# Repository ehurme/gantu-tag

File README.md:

<h1 align="center">gantu-tag · ಗಂಟು</h1>

<p align="center"><b>Open, tiny Bluetooth LE tracking tags for insects that anyone can order from JLCPCB.</b></p>

*Gantu* (ಗಂಟು, said *gun-two*) is Kannada for a knot, for someone who clings on and goes wherever you go, and for
a node.
[More about the name](#about-the-name).

**Website:** https://pvnkmrksk.github.io/gantu-tag/ · **Build guide:** [step by step](docs/guide.md)
([on the website](https://pvnkmrksk.github.io/gantu-tag/guide.html), with a form that turns your key into a config) ·
**Dashboard:** [Gantumoote](https://github.com/pvnkmrksk/gantumoote), self-hosted on a Pi or laptop

These are **early pilots**. The first panels were ordered on 6 November 2026 and arrived assembled on 19 November;
bench testing has started. **First result, the same evening:** a Hagalu S6, configured over UART and run from RAM
with a plain copper antenna, was picked up by passing iPhones and reported through Apple Find My three times in
20 minutes (±76–102 m). It advertised steadily from about 1.9 klx, and weighs **0.242 g** with its wire antenna
(tail cut, no epoxy). Treat every other number here as a design estimate until bring-up is complete.

**First walk, 20 November:** two burned Hagalu tags, running on light alone, went for a walk through town: one on
Apple Find My, one on Hubble. Both were reported, including from inside a supermarket under ordinary shop lighting.
Find My gave well over a hundred sightings in the afternoon; Hubble gave fewer (25 packets), but each one carried the
relaying phone's GPS fix and the tag's own encrypted payload: supply voltage and temperature.

| Find My: the track | Find My: sightings | Hubble: a packet and its decoded payload |
|---|---|---|
|  |  |  |

| Weighed: 0.242 g | Advertising Find My under 1.7 klx |
|---|---|
|  |  |

## The two tags

| | **Hagalu Gantu** · ಹಗಲು ಗಂಟು | **Irulu Gantu** · ಇರುಳು ಗಂಟು |
|---|---|---|
| Power | Six photodiodes charge a 100 µF capacitor; no battery | A silver-oxide button cell (337, 364 or 377) |
| When it runs | **In light only**, in bursts as the capacitor fills | Continuously until the cell is flat (≈ 57 days on a 337 at a 3 s interval) |
| Size (after cutting the tail) | 6.4 × 12.55 mm | Ø 7.2 mm |
| Mass (0.6 mm board) | **0.242 g measured** (S6 with wire, no epoxy; estimate was 0.19–0.21 g) | ≈ 0.12 g without the cell, ≈ 0.25 g with a 337 (estimate) |
| **Cost per tag** (approx.) | **≈ €7** | **≈ €2.30** + a button cell |
| Start-up | On S6/S6L a supervisor starts the radio once the capacitor holds a burst; N6 has none | Fit the cell (V1), or cut the tail (V2) |
| Pilot variants on the panel | S6, S6L, N6 | V1, V2 |
| Design files | [`hagalu/`](hagalu/) | [`irulu/`](irulu/) |

### Renders

KiCad 10 renders of the v8.3 boards as ordered. Top: parts side. Bottom: the antenna pads on Hagalu, and the cell
pads on Irulu.

| | Top | Bottom |
|---|---|---|
| **Hagalu Gantu** |  |  |
| **Irulu Gantu** |  |  |

The JLC panel (94.9 × 71.1 mm, 0.6 mm), with 10 Hagalu and 8 Irulu tags on each panel:

The pilot variant names (S6, S6L, N6, V1, V2) only mark the start-circuit options under test. They'll be narrowed
down once the first tags are on the bench.

## Approach

The tag doesn't carry a GPS or a receiver. It only **broadcasts a Bluetooth LE advert every few seconds**, and phones
or gateways that belong to a large existing network hear it and report where they were. You then fetch those
reports.

- **One chip, configured rather than programmed.** Both tags use the InPlay
  [IN100 NanoBeacon](https://inplay-tech.com/in100). It runs no firmware: you load a configuration over its UART
  (address, advert bytes, interval, TX power), test it in RAM, then burn it once into the chip's one-time-programmable
  memory. That keeps the tag down to the chip, a crystal and a few capacitors.
- **Two networks, the same hardware.** Which network a tag joins is decided only by what you burn into it:
  - **Apple Find My** via [OpenHaystack](https://github.com/seemoo-lab/openhaystack): the tag sends a fixed-key
    Find My advert, nearby iPhones relay its position to Apple, and you decrypt the reports with your private key.
    No Apple hardware is needed on the tag side, and it costs nothing per tag.
  - **[Hubble Network](https://hubble.com)**: the IN100 is one of Hubble's supported chips, and its adverts are picked
    up by Hubble's terrestrial network of phones and gateways and, as its next satellites arrive, from orbit. Hubble
    is a paid service with a free starter tier.
- **Built by JLCPCB, finished by hand.** Every part is placed by JLCPCB's assembly service from its own stock, on a
  2-layer 0.6 mm board. You add only the antenna wire, the cell (Irulu) and epoxy.
- **Started by cutting.** Each tag carries its programming pads on a tail. Like commercial bat and insect tags, you
  program it, then cut the tail off; on Irulu V2 the cut is also what switches it on.
- **Pilots before a batch.** The first panel carries several population variants of each tag (S6/S6L/N6 and V1/V2),
  so one order shows which start circuit works before anyone orders in bulk.

## Build your own

The [build guide](docs/guide.md) walks through every step, with photos. In short:

1. **Order** the files in [`order/`](order/) from JLCPCB: 0.6 mm, Panel by Customer, Standard PCBA, 2 assembled
   panels. One order gives 20 Hagalu and 16 Irulu tags.
2. **Fit the antenna:** a 31 mm, ≈ 0.1 mm wire on the **ANT** pad, and a second one on **GND** for a dipole.
3. **Make the jig:** four jumper wires, a 2 × 2 block of header pins and a rubber band. The pins wedge into the
   tail's four 0.8 mm holes and hold by themselves.
4. **Make the config:** take a template from [`configs/`](configs/) and add your key, from Find My (you generate it)
   or Hubble (it issues one). Use `tools/new_findmy_tag.py` or `tools/new_hubble_tag.py`, or the website's form.
5. **Program:** InPlay's NanoBeacon Config Tool. Test in RAM, then burn the one-time-programmable memory
   ([details](docs/programming.md)).
6. **Finish:** fit the cell on Irulu, cut the tail, coat in epoxy. Then follow the tag through Find My or Hubble.

| The jig | Wiring: tail → 3.3 V USB-serial adapter |
|---|---|
|  | **G** (square hole) → GND<br>**+** → 3V3 (never 5 V)<br>**R** → TXD<br>**T** → RXD<br><br>Seat the jig first, then plug in the USB. |

## Follow your tags

[Gantumoote](https://github.com/pvnkmrksk/gantumoote), the self-hosted dashboard in its own repository, is the map we used for the first walk. Run it on a laptop or leave
it collecting on a Raspberry Pi. It handles Find My and Hubble in the same device list, including voltage,
temperature and advert count from the Gantu Hubble payload. Each tag keeps its own history. Your keys, history
and logs stay on the host. A Pi can start collecting at boot and keep the same HTTPS address through a named tunnel.

## Roadmap

Lighter first, then simpler, then cheaper. The full plan, with mass targets, is in [`docs/roadmap.md`](docs/roadmap.md).

| Stage | What | Hagalu | Irulu (with a 337) |
|---|---|---|---|
| **Now** | Bench work on the v8.3 pilots: mass split, Irulu bring-up, S6L/N6, a smaller C1, range; nitinol antenna wire and silver-epoxy joints instead of solder | 0.242 g measured | ≈ 0.25 g |
| **v9** | Polyimide flex, antenna as a trace on a flex tail, thinner copper, 47 µF C1 if it tests well | ≈ 0.13–0.16 g | ≈ 0.19–0.20 g |
| **v10** | IN100 in WLCSP (1.1 × 2.0 mm), 0201 parts; Irulu no bigger than its cell | ≈ 0.05–0.07 g | ≈ 0.16–0.17 g |

On Irulu the 0.13 g cell is the floor; everything else can shrink to ≈ 0.03–0.04 g.

## Repository map

| Folder | What's in it |
|---|---|
| [`hagalu/`](hagalu/) | Solar tag: KiCad project, the Python that generates it (`tools/design.py`), solar simulation, renders, review |
| [`irulu/`](irulu/) | Battery tag: KiCad project, generator, burst simulation, renders, review |
| [`v9/`](v9/) | Draft KiCad projects for Hagalu S6 flex, Irulu 337, and Irulu larger-cell |
| [`panel/`](panel/) | The combined 0.6 mm JLC panel (KiKit layout, mixed-variant BOM/CPL) and its ordering README |
| [`order/`](order/) | The exact files sent to JLCPCB, with a checksum |
| [`configs/`](configs/) | Find My and Hubble config templates for InPlay's Config Tool: add your key |
| [`tools/`](tools/) | Make a tag's key and config (`new_findmy_tag.py`, `new_hubble_tag.py`); decode a Hubble advert (`hubble_decode.py`) |
| [`docs/`](docs/) | [Build guide](docs/guide.md), [programming](docs/programming.md), [roadmap](docs/roadmap.md), [tag records](docs/tags.md), the v8 handover and build notes, photos, the logo |
| [`site/`](site/) | The website ([publish it](site/publish.sh) to the `gh-pages` branch) |

## History

Every revision is a commit, dated when it was made. The commit that closes each version:

| Version | What changed |
|---|---|
| [`v4`](https://github.com/pvnkmrksk/gantu-tag/tree/ffad947) | 6.4 mm round tag on a 0.6 mm board, printed antenna arm, cut-off programming tab |
| [`v5`](https://github.com/pvnkmrksk/gantu-tag/tree/3f6ccb6) | 8 mm tag with a 30 mm wire antenna; all parts on the top side, cell underneath |
| [`v6`](https://github.com/pvnkmrksk/gantu-tag/tree/cb1977e) | 7 mm tag with a Blu Bat-style **cut-to-start tail** (superseded: pour and decoupling faults, don't order) |
| [`v7`](https://github.com/pvnkmrksk/gantu-tag/tree/bdc53f7) | Fixes v6; any button cell; five population variants on one test panel |
| [`v8.3`](https://github.com/pvnkmrksk/gantu-tag/tree/761deb4) | Split into **Hagalu** (solar) and **Irulu** (battery) on one combined 0.6 mm panel. **This is what was ordered** |

Before v8 there was only the battery tag, so its history lives in `irulu/`. Click a version to browse it, or
`git checkout cb1977e` for v6, for example.

## Bill of materials and cost

Per-tag parts lists with LCSC numbers are on the [website](https://pvnkmrksk.github.io/gantu-tag/#bom); the full
panel BOM is [`panel/fab/jlcpcb_panel/insect_tag_v8_combined_panel_bom.csv`](panel/fab/jlcpcb_panel/insect_tag_v8_combined_panel_bom.csv).
Approximate cost per tag, parts and JLC placement, at November 2026 prices:

| | Per tag |
|---|---|
| **Hagalu Gantu** (solar) | **≈ €7** |
| **Irulu Gantu** (button cell) | **≈ €2.30**, plus the cell you fit yourself |

Each order also carries one-off fees of roughly €100 (setup, stencil, extended-part fees, bare boards), which you
spread over however many tags you order. The first order (5 bare panels, 2 assembled, 36 tags) came to about
**€250–280 before shipping and VAT**. Most of the cost is the IN100 (≈ $2.60) and, on Hagalu, the six photodiodes
(≈ $0.87 each). The JLC cart is the real number.

## Licence

**Open, and it has to stay open.** You can use, change, build, sell and share all of it, commercially or not, on two
conditions that pass on to everything made from it:

1. **Credit the author.** Keep the [`NOTICE`](NOTICE) file and credit the work wherever you publish, show or sell
   it or anything made from it:

   > Based on gantu-tag by Pavan Kumar Kaushik, https://github.com/pvnkmrksk/gantu-tag

2. **Share alike.** Release what you make from it under the same licence, with its source.

| What | Licence |
|---|---|
| **Hardware:** KiCad projects, Gerbers, BOM and placement files, the panel, the order files, the tag configs in `configs/` | [CERN-OHL-S-2.0](LICENSE), strongly reciprocal: boards and tags made from the design count too |
| **Documentation and media:** the docs, photos, renders, PDFs, the logo, the website's text and images | [CC BY-SA 4.0](LICENSE-DOCS) |
| **Software:** `tools/`, `*/tools/`, the review scripts, `docs/logo/make_logo.py`, the website's code | [AGPL-3.0-or-later](LICENSE-CODE): also covers modified copies run as a web service. The dashboard, [Gantumoote](https://github.com/pvnkmrksk/gantumoote), is AGPL too |

Two conditions in [`NOTICE`](NOTICE) make the credit concrete: anyone who sells or hands out tags made from the
design must include the source link and the credit line in the packaging or documentation, and modified software
must keep the credit in its source and in its legal notices.

Versions up to commit `53f775e` (20 November 2026) were published under CC BY 4.0 and MIT, and copies of those keep
those terms; everything after is under the licences above. The circuits follow InPlay's IN100 datasheet and the
component values on SparkFun's NanoBeacon board; no SparkFun design files are included. There's no warranty: you
build and use these at your own risk.

## About the name

**Gantu** (ಗಂಟು, *gun-two*, /ɡəɳʈu/) works on three levels:

- **A knot.** The tag is tied onto the animal.
- **Clinging on.** Colloquially, someone who is *gantu* to you sticks to you and goes wherever you go, as if the two of
  you were knotted together. That's the tag and its insect.
- **A node,** as on a plant stem or in a network. The tag is found as a node heard by a mesh of phones and gateways.

**Hagalu** (ಹಗಲು, *huh-guh-loo*, /ɦəɡəlu/, day) and **Irulu** (ಇರುಳು, *ih-roo-loo*, /iruɭu/, night) name how each
tag works: Hagalu runs on daylight, Irulu runs on its cell through the night as well.

The *ṇṭ* in gantu is retroflex (tongue curled back), as is the *ḷ* in irulu. The logo is one thread tied in a trefoil
knot, shading from turmeric ochre into indigo.

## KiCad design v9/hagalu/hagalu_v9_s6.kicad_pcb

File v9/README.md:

# v9 KiCad projects

Open the `.kicad_pro` in KiCad 10. Each project has a schematic, a PCB with a removable programming tail, and local symbol, footprint and 3D model files. The tails use Ø0.95 mm surface pads on 1.80 mm pitch. The [v8.3 bench checklist](../docs/roadmap.md#stage-0-bench-work-on-the-v83-boards-now) controls the remaining PCB decisions. The v9 project files are their own source. The v8 generators still target the pilot boards.

| Project | Saved PCB draft | Before fabrication |
|---|---|---|
| [Hagalu S6 flex](hagalu/hagalu_v9_s6.kicad_pro) · [render](renders/hagalu-s6.png) | 6.55 × 13.68 mm body, with a 6.32 mm-wide photodiode section and nominal 0.11 mm polyimide stackup. The tail has VCC and CHIP_EN probe pads beside the programming pads. | Qualify the ½ oz copper stackup, radio and crystal stiffener, and supported pogo contacts. Design the hatched ground and the printed-trace trial alongside the glued 0.10 mm wire reference. Use bench data to decide on the 47 µF C1 and alternate photodiode counts. |
| [Irulu 337](irulu-337/irulu_v9_337.kicad_pro) · [render](renders/irulu-337.png) | Ø6.75 mm circular body with underside contacts for a 4.8 mm 337 (SR416). The QFN18 and 0402 decoupling capacitor are retained. The v8.3 V1 enable is the reference at 0 dBm on one network. | Choose V1 or V2 after measuring CHIP_EN and qualify the rim contact and insulation. Choose rigid or flex for mechanical support. The saved PCB uses the default 1.6 mm thickness as a placeholder. Confirm custom panelization for this size with the fab. |
| [Irulu larger cell](irulu-large-cell/irulu_v9_large_cell.kicad_pro) · [render](renders/irulu-larger-cell.png) | Ø10.00 mm circular body on a 0.6 mm rigid draft. The negative contact is underneath and the positive strap pad is on top. | Choose the exact 7.9–9.5 mm cell, insulate the positive pad from the can, and verify contact support and startup. Qualify the +4 dBm, three-network profile on the bench. |

## Hagalu light-sensing trial

All seven photodiode footprints use Vishay's TEMD7000X01 land pattern, with 1.00 × 1.45 mm pads and a 0.60 mm gap. [Vishay TEMD7000X01 datasheet, page 4](https://www.vishay.com/docs/81951/temd7000.pdf#page=4)

PD7 is a separate photovoltaic sensor. R3 loads it to ground and R4 limits current into U1 pin 5 (MGPIO5, ADC channel 1). PD7, R3 and R4 are marked DNP. Fit them together for the trial and check the ADC reading in RAM, the input with VCC off, and the effect on cold startup. R3 and R4 are provisional 100 kΩ values. InPlay limits VCC to 3.0 V for external analog measurements. Keep the 3.3 V programming session separate from ADC measurements. [InPlay IN100 datasheet, tables 1 and 2 and §4.4.3](https://www.inplay-tech.com/IN100_datasheet.pdf)

The QFN18 exposes the light-sensing input while retaining RXD and TXD. The DFN8 pins that could otherwise serve as analog inputs are assigned to UART in that package. Keep the QFN18 for this Hagalu draft and qualify DFN8 separately for Irulu. [InPlay IN100 pin assignments](https://www.inplay-tech.com/IN100_datasheet.pdf#page=12)

## Check the projects

The paired renders show the top and underside of each saved layout. Recreate them with `sh v9/render.sh` from the repository root using KiCad 10 and ImageMagick. Set `KICAD_CLI` if KiCad is installed in a custom location.

Run `sh v9/check.sh` after each change. It checks schematic ERC, PCB design rules, unrouted connections and schematic parity on all three projects. Pass a report directory as the first argument to retain the JSON reports there. Hagalu uses 0.30 mm copper-to-edge clearance for the flex outline. The other rules and net classes inherit the v8.3 defaults. Confirm the selected fabrication rules and stackups before releasing any board. [JLCPCB flex capabilities](https://jlcpcb.com/capabilities/flex-pcb-capabilities/)

Run `python3 v9/check-tail.py` with KiCad's `pcbnew` Python bindings to check Hagalu and Irulu 337 after simulated tail removal. On macOS, use `/Applications/KiCad/KiCad.app/Contents/Frameworks/Python.framework/Versions/3.9/bin/python3.9` if the system Python lacks the bindings. The script clips copper in temporary copies at each board's neck and checks the surviving connections.

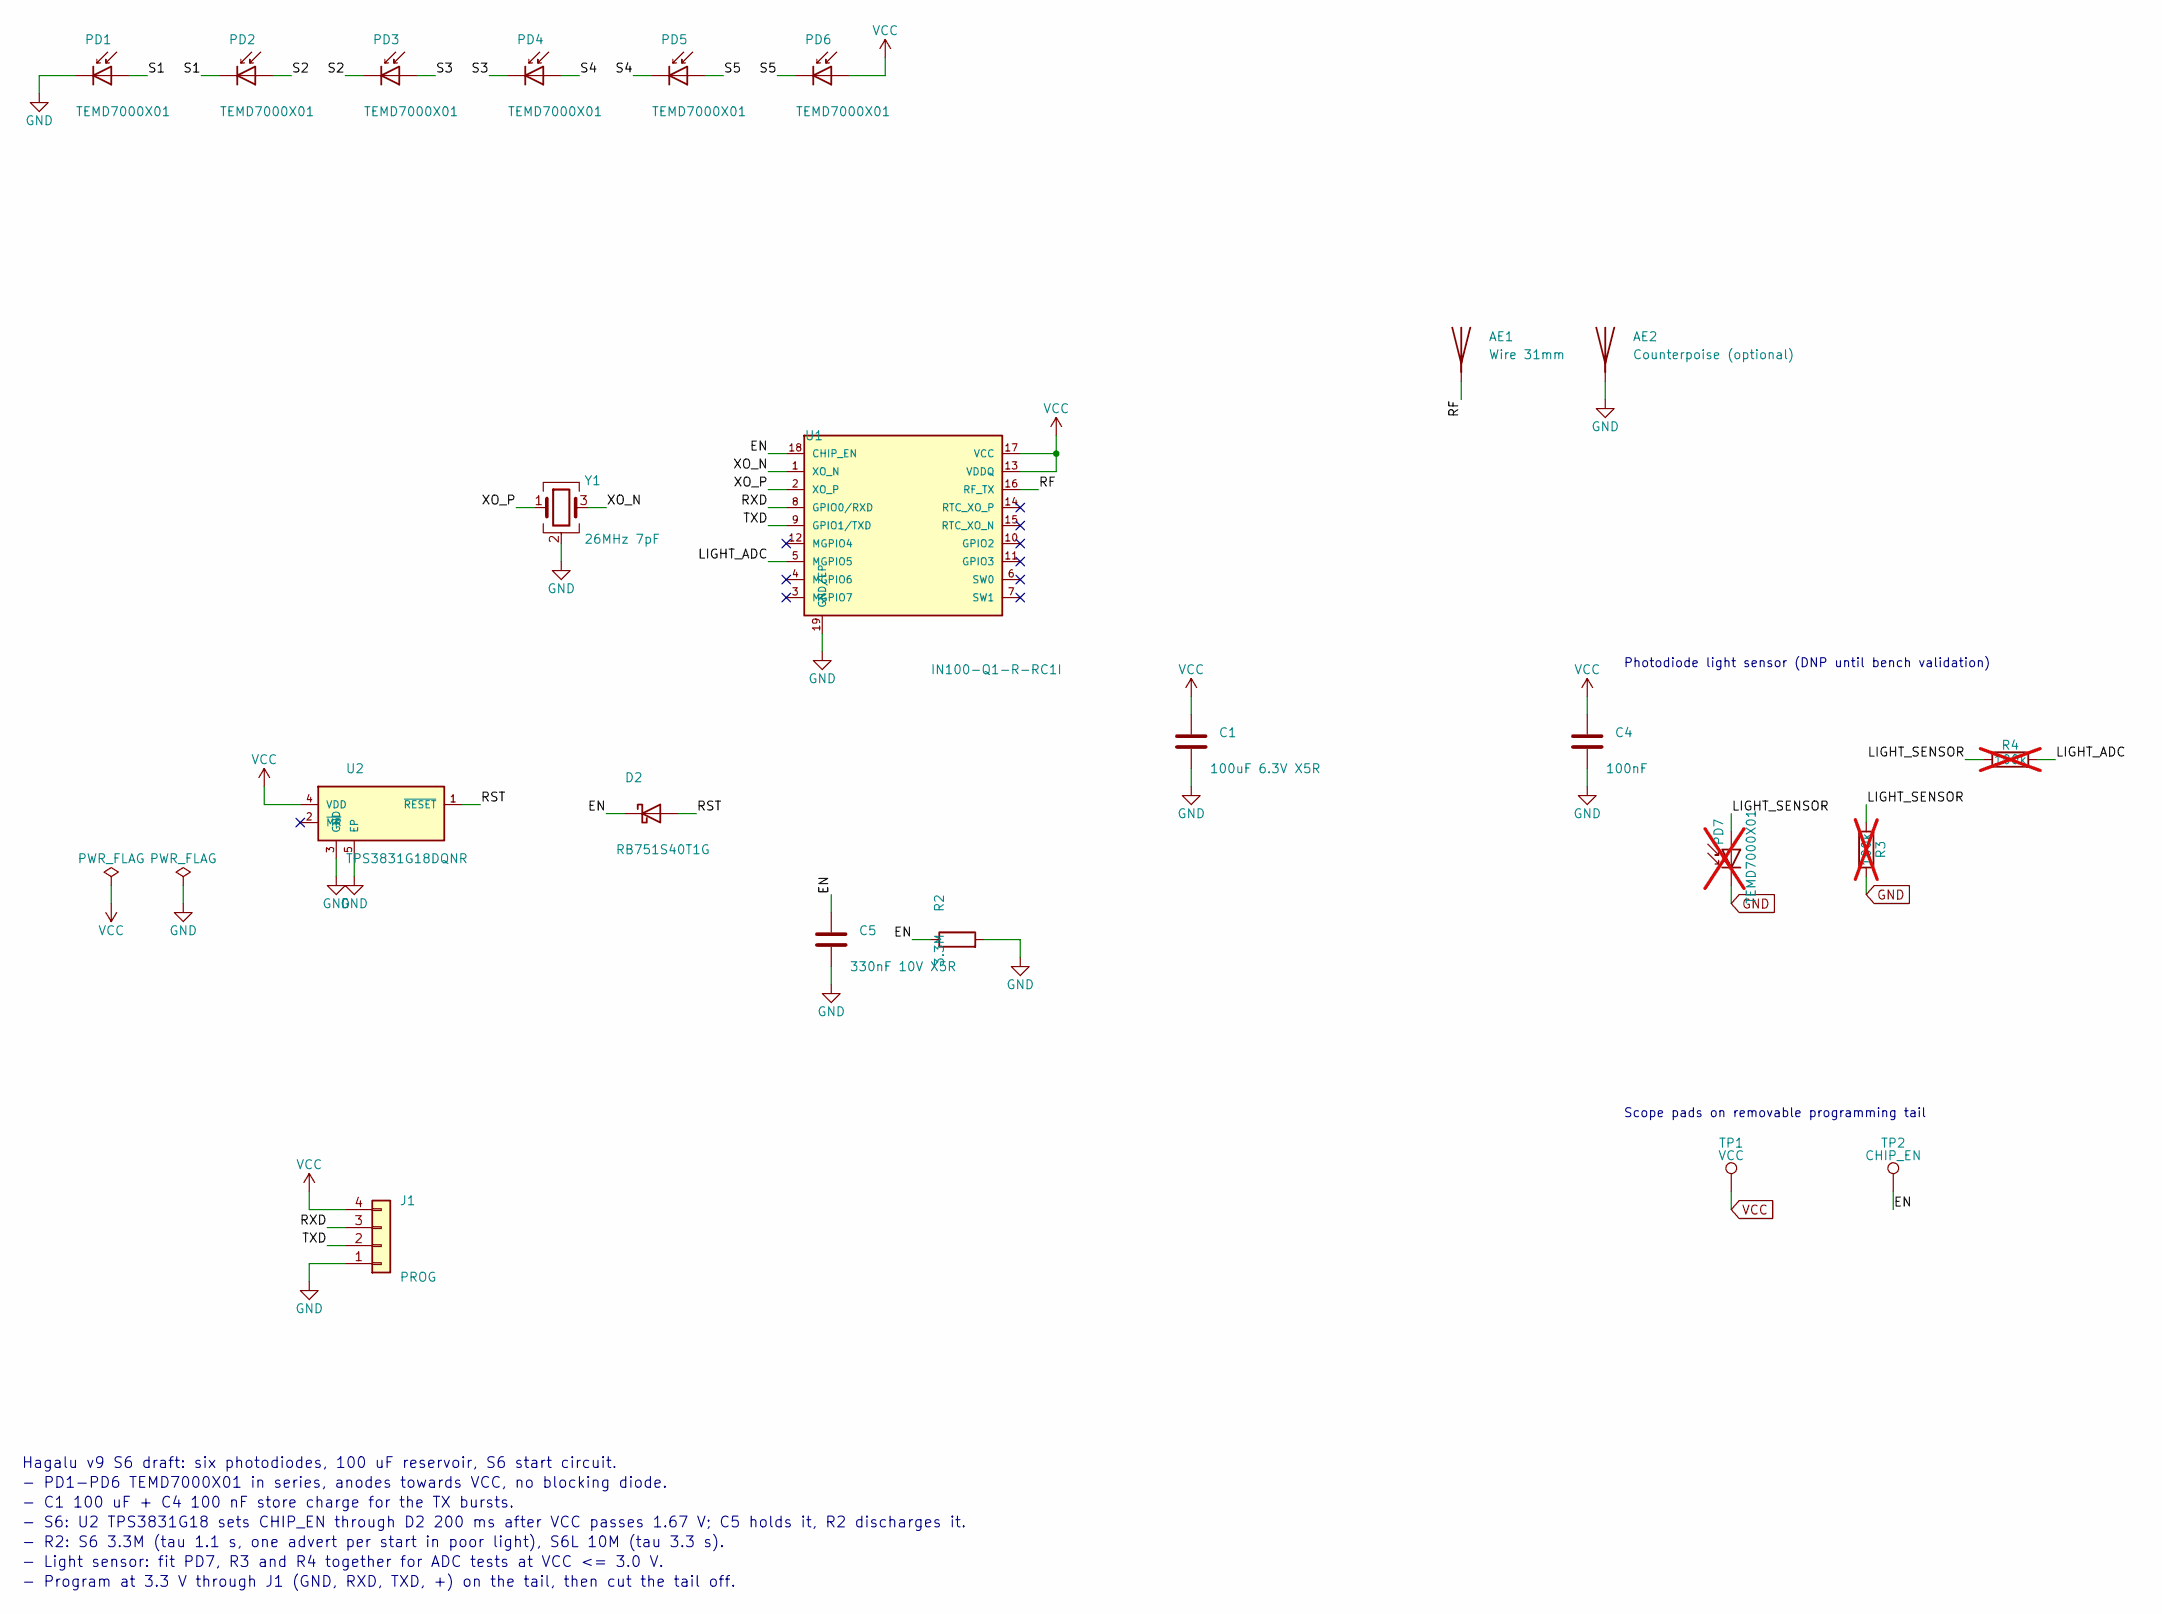
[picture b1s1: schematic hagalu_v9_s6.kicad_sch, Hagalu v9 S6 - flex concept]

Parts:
AE1: Wire 31mm; WirePadB_Edge_1p2x1p0mm
AE2: Counterpoise (optional); WirePadB_Edge_1p2x1p0mm
C1: 100uF 6.3V X5R; C_0805_2012Metric; MPN GRM21BR60J107ME15L; LCSC C141660
C4: 100nF; C_0402_1005Metric; MPN CL05B104KO5NNNC; LCSC C1525
C5: 330nF 10V X5R; C_0402_1005Metric; MPN CC0402KRX5R6BB334; LCSC C107013
D2: RB751S40T1G; D_SOD-523; MPN RB751S40T1G; LCSC C232576
J1: PROG; ProgPads_2x02_P1p80_D0p95_SMD
PD1, PD2, PD3, PD4, PD5, PD6: TEMD7000X01; PD_0805_TEMD7000; MPN TEMD7000X01; LCSC C145328
PD7: TEMD7000X01; PD_0805_TEMD7000; MPN TEMD7000X01; LCSC C145328; not fitted
R2: 3.3M; R_0402_1005Metric; MPN 0402WGF3304TCE; LCSC C270613
R3, R4: 100k; R_0402_1005Metric; not fitted
TP1: VCC; TestPoint_Pad_D1.0mm
TP2: CHIP_EN; TestPoint_Pad_D1.0mm
U1: IN100-Q1-R-RC1I; InPlay_IN100_QFN-18-1EP_3x3mm_P0.4mm_EP1.5x1.7mm; MPN IN100-Q1-R-RC1I; LCSC C6062024
U2: TPS3831G18DQNR; Texas_X2SON-4_1x1mm_P0.65mm; MPN TPS3831G18DQNR; LCSC C2066667
Y1: 26MHz 7pF; Crystal_SMD_1612-4Pin_1.6x1.2mm; MPN 8Q26000008; LCSC C5203638

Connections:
/EN: C5.1, D2.1 (K), R2.1, TP2.1, U1.18 (CHIP_EN)
/LIGHT_ADC: R4.2, U1.5 (MGPIO5)
/LIGHT_SENSOR: PD7.2 (A), R3.1, R4.1
/RF: AE1.1, U1.16 (RF_TX)
/RST: D2.2 (A), U2.1 (~RESET)
/RXD: J1.3, U1.8 (GPIO0/RXD)
/S1: PD1.2 (A), PD2.1 (K)
/S2: PD2.2 (A), PD3.1 (K)
/S3: PD3.2 (A), PD4.1 (K)
/S4: PD4.2 (A), PD5.1 (K)
/S5: PD5.2 (A), PD6.1 (K)
/TXD: J1.2, U1.9 (GPIO1/TXD)
/XO_N: U1.1 (XO_N), Y1.3
/XO_P: U1.2 (XO_P), Y1.1
GND: AE2.1, C1.2, C4.2, C5.2, J1.1, PD1.1 (K), PD7.1 (K), R2.2, R3.2, U1.19 (GND/EP), U2.3 (GND), U2.5 (EP), Y1.2 (G), Y1.4 (G)
VCC: C1.1, C4.1, J1.4, PD6.2 (A), TP1.1, U1.13 (VDDQ), U1.17 (VCC), U2.4 (VDD)

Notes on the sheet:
Hagalu v9 S6 draft: six photodiodes, 100 uF reservoir, S6 start circuit.
- PD1-PD6 TEMD7000X01 in series, anodes towards VCC, no blocking diode.
- C1 100 uF + C4 100 nF store charge for the TX bursts.
- S6: U2 TPS3831G18 sets CHIP_EN through D2 200 ms after VCC passes 1.67 V; C5 holds it, R2 discharges it.
- R2: S6 3.3M (tau 1.1 s, one advert per start in poor light), S6L 10M (tau 3.3 s).
- Light sensor: fit PD7, R3 and R4 together for ADC tests at VCC <= 3.0 V.
- Program at 3.3 V through J1 (GND, RXD, TXD, +) on the tail, then cut the tail off.
Photodiode light sensor (DNP until bench validation)
Scope pads on removable programming tail

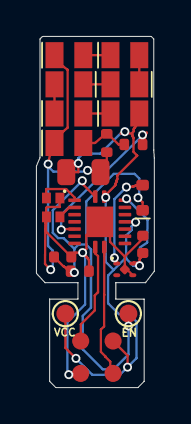
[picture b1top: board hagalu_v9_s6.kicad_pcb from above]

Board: 2 copper layers, 6.5 x 19.5 mm, 22 parts (0 on the bottom side), 16 nets.

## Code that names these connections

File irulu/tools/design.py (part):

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         ref_at=(2, -5, "left"), val_at=(2, 3.5, "left")),
]

# U1 (QFN18): 1 XO_N, 2 XO_P, 3-7 NC, 8 GPIO0 (RXD), 9 GPIO1 (TXD), 10-12 NC, 13 VDDQ, 14/15 RTC (NC), 16 RF_TX,
# 17 VCC, 18 CHIP_EN, 19 EP/GND
NETS = {
    "VCC":  [("U1", "17"), ("U1", "13"), ("C1", "1"), ("C4", "1"), ("R1", "2"), ("BT1", "1"), ("J1", "4")],
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

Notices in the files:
v9/hagalu/hagalu_v9_s6.kicad_sch:
CERN-OHL-S-2.0. (C) 2026 Pavan Kumar Kaushik.
